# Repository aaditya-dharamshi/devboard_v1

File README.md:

# devboard_v1
STM32 devboard, originally developed for FIA SeeGoals

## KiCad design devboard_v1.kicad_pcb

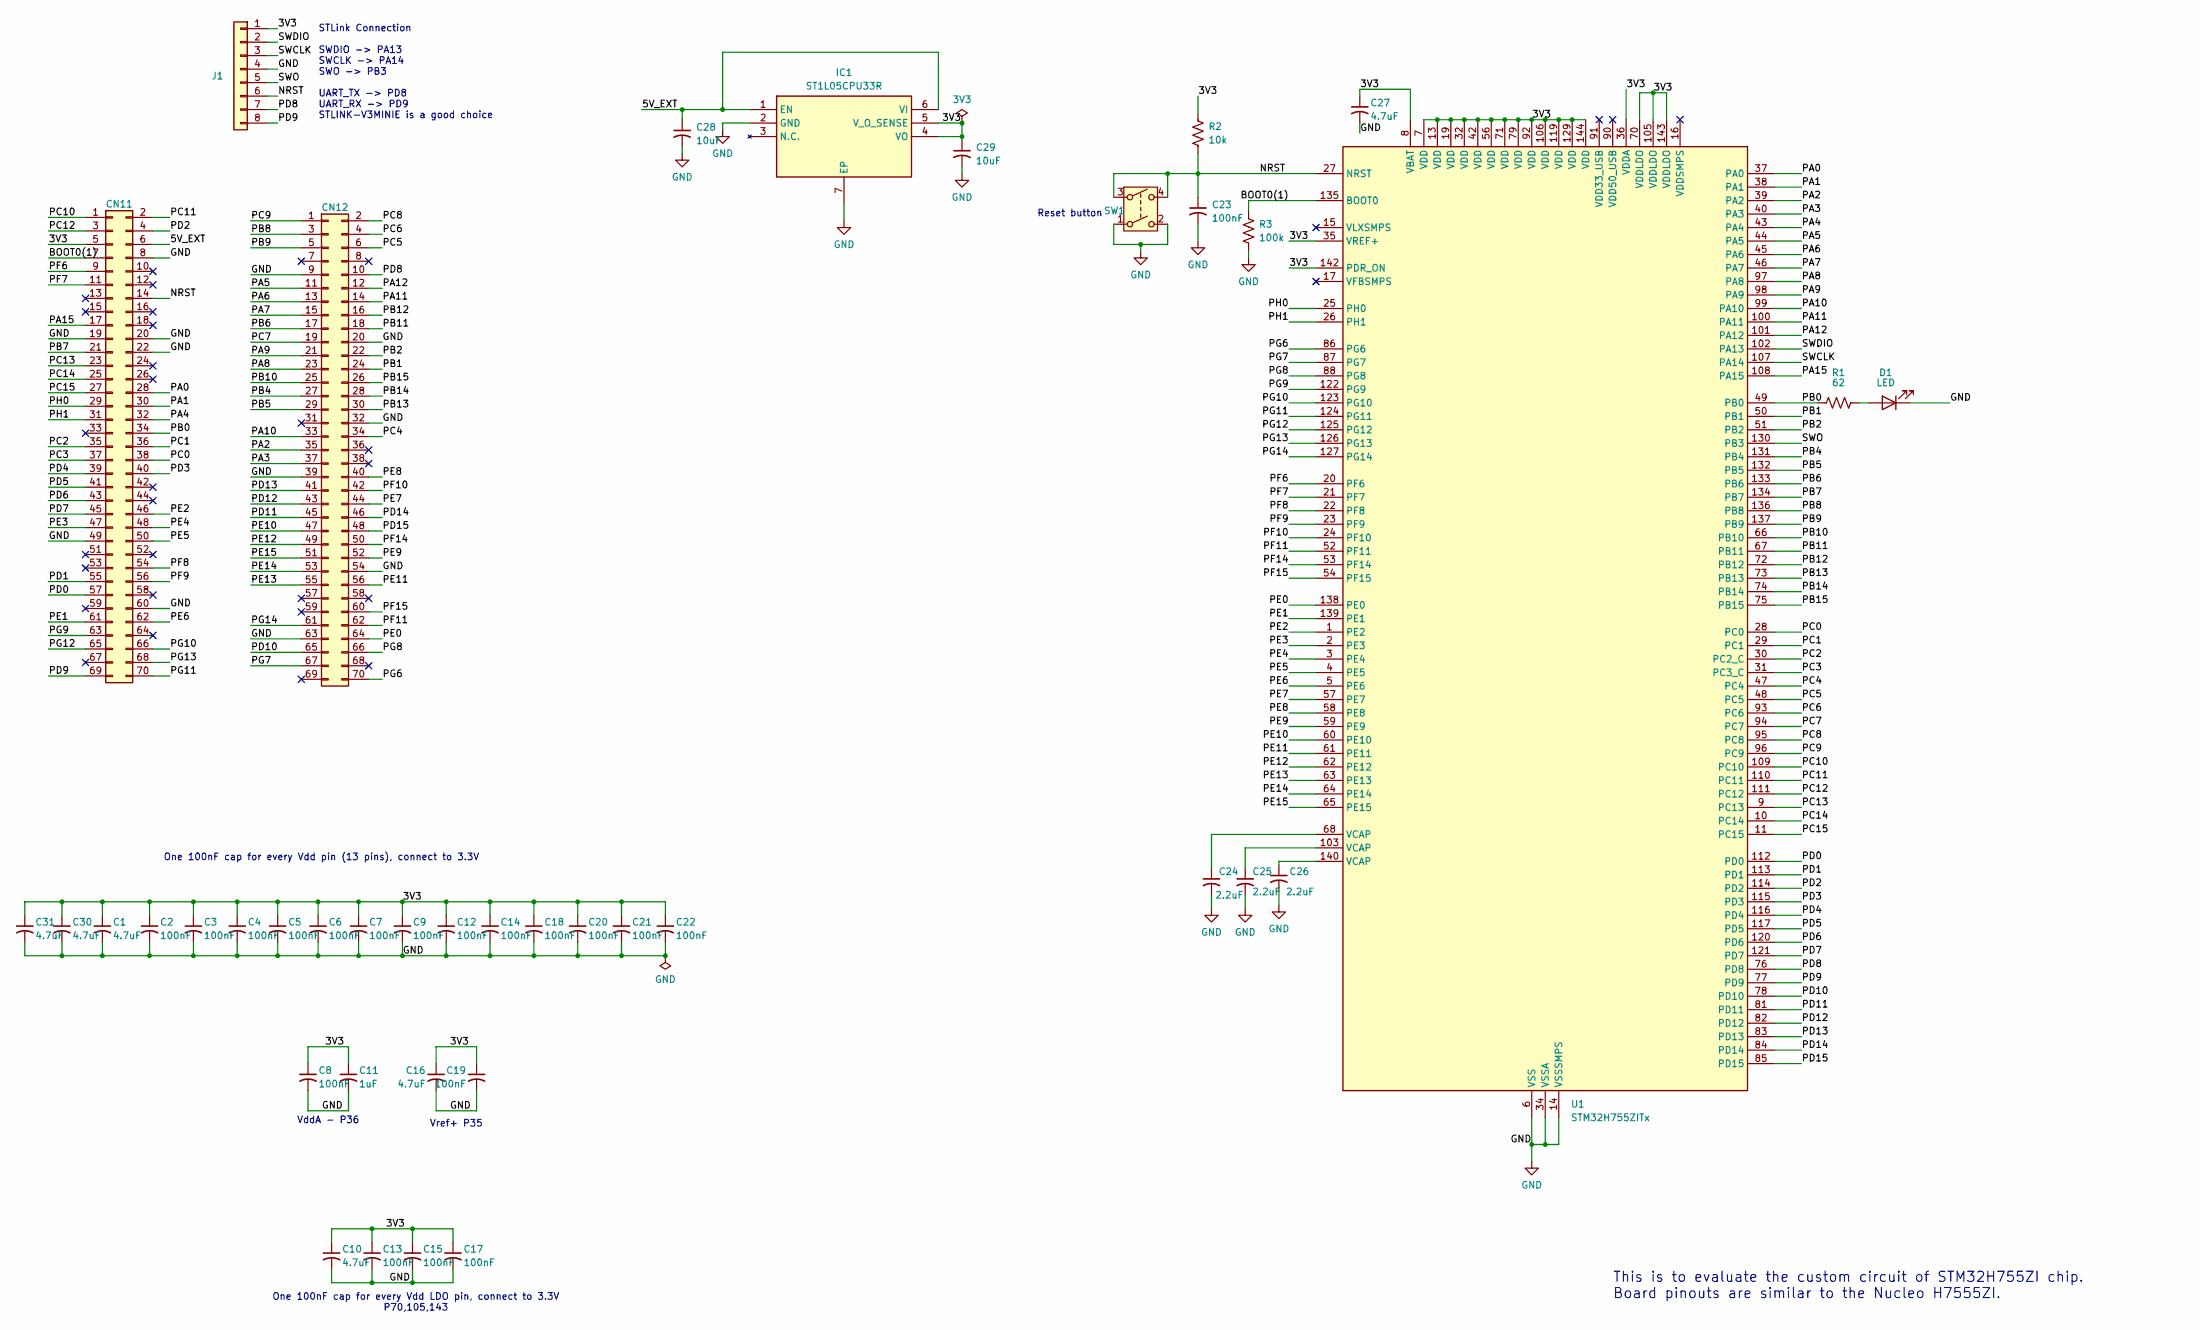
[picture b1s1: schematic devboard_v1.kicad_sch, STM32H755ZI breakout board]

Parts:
C1, C10, C16, C27, C30, C31: 4.7uF; C_0402_1005Metric; JLCPCB C23733
C2, C3, C4, C5, C6, C7, C8, C9, C12, C13, C14, C15, C17, C18, C19, C20, C21, C22, C23: 100nF; C_0402_1005Metric; JLCPCB C1525
C11: 1uF; C_0402_1005Metric; JLCPCB C14445
C24, C25, C26: 2.2uF; C_0402_1005Metric; JLCPCB C107369
C28, C29: 10uF; C_0402_1005Metric; JLCPCB C315248
CN11, CN12: Conn_02x36_Counter_Clockwise; PinHeader_2x35_P2.54mm_Vertical
D1: LED; LED_0603_1608Metric; JLCPCB C2286
IC1: ST1L05CPU33R; SON95P300X300X100-7N-D; Manufacturer_Part_Number ST1L05CPU33R; Mouser Part Number 511-ST1L05CPU33R
J1: Conn_01x08; PinSocket_1x08_P2.54mm_Vertical
R1: 62; R_0402_1005Metric; JLCPCB C412968
R2: 10k; R_0402_1005Metric; JLCPCB C71617
R3: 100k; R_0402_1005Metric; JLCPCB C191569
SW1: CK_KMS2xxG; TPS645-5NC105_JLCPCB; JLCPCB C19191549
U1: STM32H755ZITx; LQFP-144_20x20mm_P0.5mm; JLCPCB C730212

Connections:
/3V3: C1.1, C2.1, C3.1, C4.1, C5.1, C6.1, C7.1, C8.1, C9.1, C10.1, C11.1, C12.1, C13.1, C14.1, C15.1, C16.1, C17.1, C18.1, C19.1, C20.1, C21.1, C22.1, C27.1, C29.1, C30.1, C31.1, CN11.5, IC1.4 (VO), IC1.5 (V_O_SENSE), J1.1, R2.1, U1.7 (VDD), U1.8 (VBAT), U1.13 (VDD), U1.19 (VDD), U1.32 (VDD), U1.35 (VREF+), U1.36 (VDDA), U1.42 (VDD), U1.56 (VDD), U1.70 (VDDLDO), U1.71 (VDD), U1.79 (VDD), U1.92 (VDD), U1.105 (VDDLDO), U1.106 (VDD), U1.119 (VDD), U1.129 (VDD), U1.142 (PDR_ON), U1.143 (VDDLDO), U1.144 (VDD)
/5V_EXT: C28.1, CN11.6, IC1.1 (EN), IC1.6 (VI)
/BOOT0(1): CN11.7, R3.1, U1.135 (BOOT0)
/NRST: C23.1, CN11.14, J1.6, R2.2, SW1.3, SW1.4, U1.27 (NRST)
/PA0: CN11.28, U1.37 (PA0)
/PA1: CN11.30, U1.38 (PA1)
/PA2: CN12.35, U1.39 (PA2)
/PA3: CN12.37, U1.40 (PA3)
/PA4: CN11.32, U1.43 (PA4)
/PA5: CN12.11, U1.44 (PA5)
/PA6: CN12.13, U1.45 (PA6)
/PA7: CN12.15, U1.46 (PA7)
/PA8: CN12.23, U1.97 (PA8)
/PA9: CN12.21, U1.98 (PA9)
/PA10: CN12.33, U1.99 (PA10)
/PA11: CN12.14, U1.100 (PA11)
/PA12: CN12.12, U1.101 (PA12)
/PA15: CN11.17, U1.108 (PA15)
/PB0: CN11.34, R1.1, U1.49 (PB0)
/PB1: CN12.24, U1.50 (PB1)
/PB2: CN12.22, U1.51 (PB2)
/PB4: CN12.27, U1.131 (PB4)
/PB5: CN12.29, U1.132 (PB5)
/PB6: CN12.17, U1.133 (PB6)
/PB7: CN11.21, U1.134 (PB7)
/PB8: CN12.3, U1.136 (PB8)
/PB9: CN12.5, U1.137 (PB9)
/PB10: CN12.25, U1.66 (PB10)
/PB11: CN12.18, U1.67 (PB11)
/PB12: CN12.16, U1.72 (PB12)
/PB13: CN12.30, U1.73 (PB13)
/PB14: CN12.28, U1.74 (PB14)
/PB15: CN12.26, U1.75 (PB15)
/PC0: CN11.38, U1.28 (PC0)
/PC1: CN11.36, U1.29 (PC1)
/PC2: CN11.35, U1.30 (PC2_C)
/PC3: CN11.37, U1.31 (PC3_C)
/PC4: CN12.34, U1.47 (PC4)
/PC5: CN12.6, U1.48 (PC5)
/PC6: CN12.4, U1.93 (PC6)
/PC7: CN12.19, U1.94 (PC7)
/PC8: CN12.2, U1.95 (PC8)
/PC9: CN12.1, U1.96 (PC9)
/PC10: CN11.1, U1.109 (PC10)
/PC11: CN11.2, U1.110 (PC11)
/PC12: CN11.3, U1.111 (PC12)
/PC13: CN11.23, U1.9 (PC13)
/PC14: CN11.25, U1.10 (PC14)
/PC15: CN11.27, U1.11 (PC15)
/PD0: CN11.57, U1.112 (PD0)
/PD1: CN11.55, U1.113 (PD1)
/PD2: CN11.4, U1.114 (PD2)
/PD3: CN11.40, U1.115 (PD3)
/PD4: CN11.39, U1.116 (PD4)
/PD5: CN11.41, U1.117 (PD5)
/PD6: CN11.43, U1.120 (PD6)
/PD7: CN11.45, U1.121 (PD7)
/PD8: CN12.10, J1.7, U1.76 (PD8)
/PD9: CN11.69, J1.8, U1.77 (PD9)
/PD10: CN12.65, U1.78 (PD10)
/PD11: CN12.45, U1.81 (PD11)
/PD12: CN12.43, U1.82 (PD12)
/PD13: CN12.41, U1.83 (PD13)
/PD14: CN12.46, U1.84 (PD14)
/PD15: CN12.48, U1.85 (PD15)
/PE0: CN12.64, U1.138 (PE0)
/PE1: CN11.61, U1.139 (PE1)
/PE2: CN11.46, U1.1 (PE2)
/PE3: CN11.47, U1.2 (PE3)
/PE4: CN11.48, U1.3 (PE4)
/PE5: CN11.50, U1.4 (PE5)
/PE6: CN11.62, U1.5 (PE6)
/PE7: CN12.44, U1.57 (PE7)
/PE8: CN12.40, U1.58 (PE8)
/PE9: CN12.52, U1.59 (PE9)
/PE10: CN12.47, U1.60 (PE10)
/PE11: CN12.56, U1.61 (PE11)
/PE12: CN12.49, U1.62 (PE12)
/PE13: CN12.55, U1.63 (PE13)
/PE14: CN12.53, U1.64 (PE14)
/PE15: CN12.51, U1.65 (PE15)
/PF6: CN11.9, U1.20 (PF6)
/PF7: CN11.11, U1.21 (PF7)
/PF8: CN11.54, U1.22 (PF8)
/PF9: CN11.56, U1.23 (PF9)
/PF10: CN12.42, U1.24 (PF10)
/PF11: CN12.62, U1.52 (PF11)
/PF14: CN12.50, U1.53 (PF14)
/PF15: CN12.60, U1.54 (PF15)
/PG6: CN12.70, U1.86 (PG6)
/PG7: CN12.67, U1.87 (PG7)
/PG8: CN12.66, U1.88 (PG8)
/PG9: CN11.63, U1.122 (PG9)
/PG10: CN11.66, U1.123 (PG10)
/PG11: CN11.70, U1.124 (PG11)
/PG12: CN11.65, U1.125 (PG12)
/PG13: CN11.68, U1.126 (PG13)
/PG14: CN12.61, U1.127 (PG14)
/PH0: CN11.29, U1.25 (PH0)
/PH1: CN11.31, U1.26 (PH1)
/SWCLK: J1.3, U1.107 (PA14)
/SWDIO: J1.2, U1.102 (PA13)
/SWO: J1.5, U1.130 (PB3)
GND: C1.2, C2.2, C3.2, C4.2, C5.2, C6.2, C7.2, C8.2, C9.2, C10.2, C11.2, C12.2, C13.2, C14.2, C15.2, C16.2, C17.2, C18.2, C19.2, C20.2, C21.2, C22.2, C23.2, C24.2, C25.2, C26.2, C27.2, C28.2, C29.2, C30.2, C31.2, CN11.8, CN11.19, CN11.20, CN11.22, CN11.49, CN11.60, CN12.9, CN12.20, CN12.32, CN12.39, CN12.54, CN12.63, D1.1 (K), IC1.2 (GND), IC1.7 (EP), J1.4, R3.2, SW1.1, SW1.2, U1.6 (VSS), U1.12 (VSS), U1.14 (VSSSMPS), U1.18 (VSS), U1.33 (VSS), U1.34 (VSSA), U1.41 (VSS), U1.55 (VSS), U1.69 (VSS), U1.80 (VSS), U1.89 (VSS), U1.104 (VSS), U1.118 (VSS), U1.128 (VSS), U1.141 (VSS)
unnamed: C24.1, U1.68 (VCAP)
unnamed: C25.1, U1.103 (VCAP)
unnamed: C26.1, U1.140 (VCAP)
unnamed: D1.2 (A), R1.2

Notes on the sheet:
VddA - P36
STLink Connection SWDIO -> PA13 SWCLK -> PA14 SWO -> PB3 UART_TX -> PD8 UART_RX -> PD9 STLINK-V3MINIE is a good choice
Vref+ P35
Reset button
One 100nF cap for every Vdd LDO pin, connect to 3.3V P70,105,143
This is to evaluate the custom circuit of STM32H755ZI chip. Board pinouts are similar to the Nucleo H7555ZI.
One 100nF cap for every Vdd pin (13 pins), connect to 3.3V

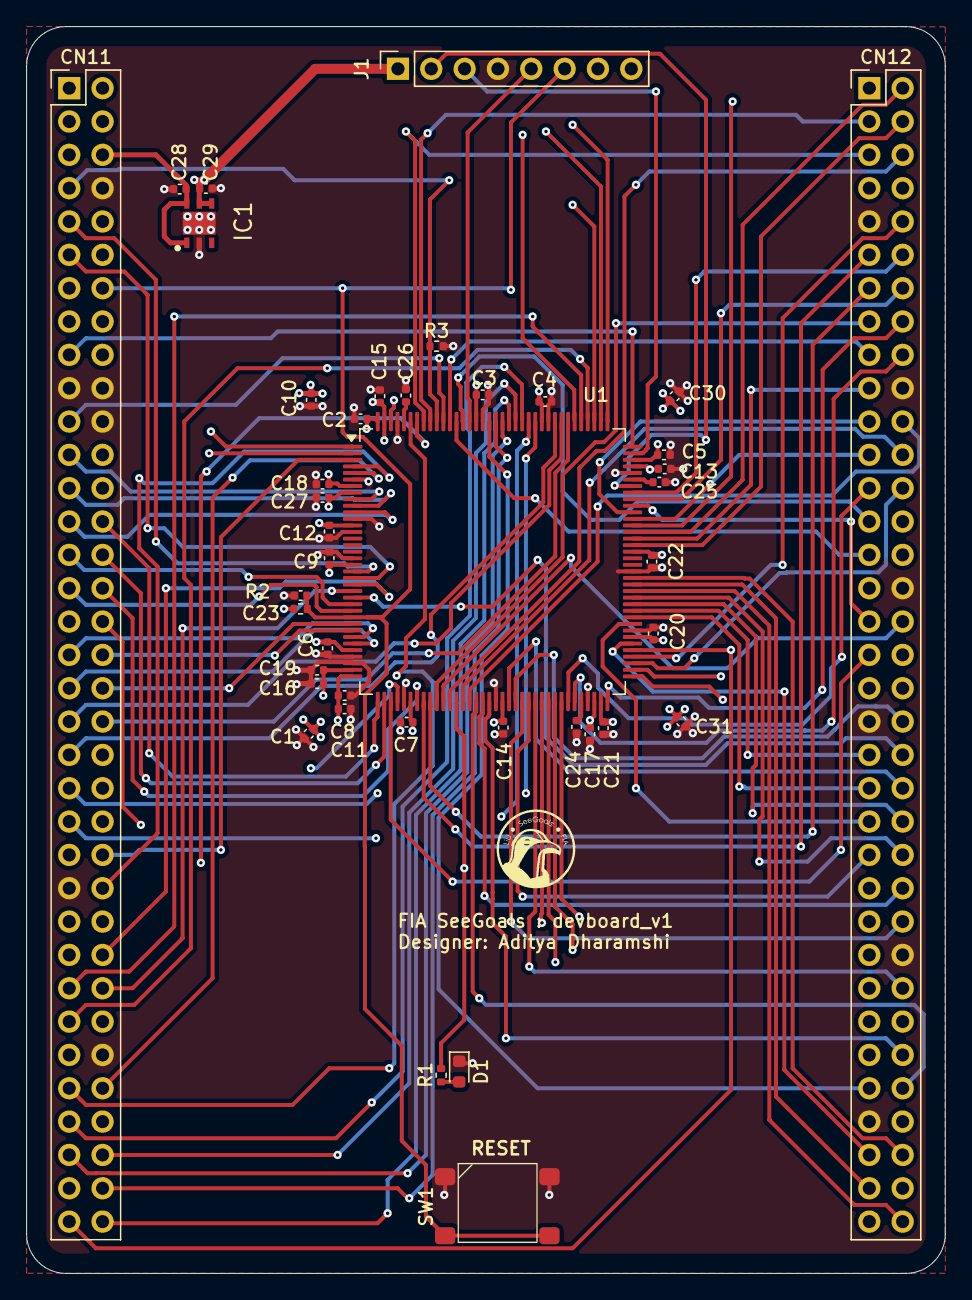
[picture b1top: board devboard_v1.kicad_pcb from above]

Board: 4 copper layers, 70.0 x 95.0 mm, 41 parts (0 on the bottom side), 108 nets.

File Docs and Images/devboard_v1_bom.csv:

Designator,Footprint,Quantity,Value,LCSC Part #
"C1, C10, C16, C27, C30, C31",402,6,4.7uF,C23733
C11,402,1,1uF,C1525
"C12, C13, C14, C15, C17, C18, C19, C2, C20, C21, C22, C23, C3, C4, C5, C6, C7, C8, C9",402,19,100nF,C14445
"C24, C25, C26",402,3,2.2uF,C107369
"C28, C29",402,2,10uF,C315248
D1,603,1,LED,C2286
IC1,SON95P300X300X100-7N-D,1,ST1L05CPU33R,C2969933 
R1,402,1,62,C412968
R2,402,1,10k,C71617
R3,402,1,100k,C191569
SW1,TPS645-5NC105_JLCPCB,1,CK_KMS2xxG,C19191549
U1,LQFP-144_20x20mm_P0.5mm,1,STM32H755ZITx,C730212

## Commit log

2026-03-02 Files uploaded
